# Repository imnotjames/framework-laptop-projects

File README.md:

# Framework Laptop projects

## eDP port

The framework laptop uses the [I-PEX Cabline-UM 20879-040E-01](https://www.i-pex.com/product/cabline-um)
for interacting with the eDP port - and I want to use it for things other than the framework laptop display kit.

* [Framework eDP 20879-040E-01 Breakout](./breakout/)

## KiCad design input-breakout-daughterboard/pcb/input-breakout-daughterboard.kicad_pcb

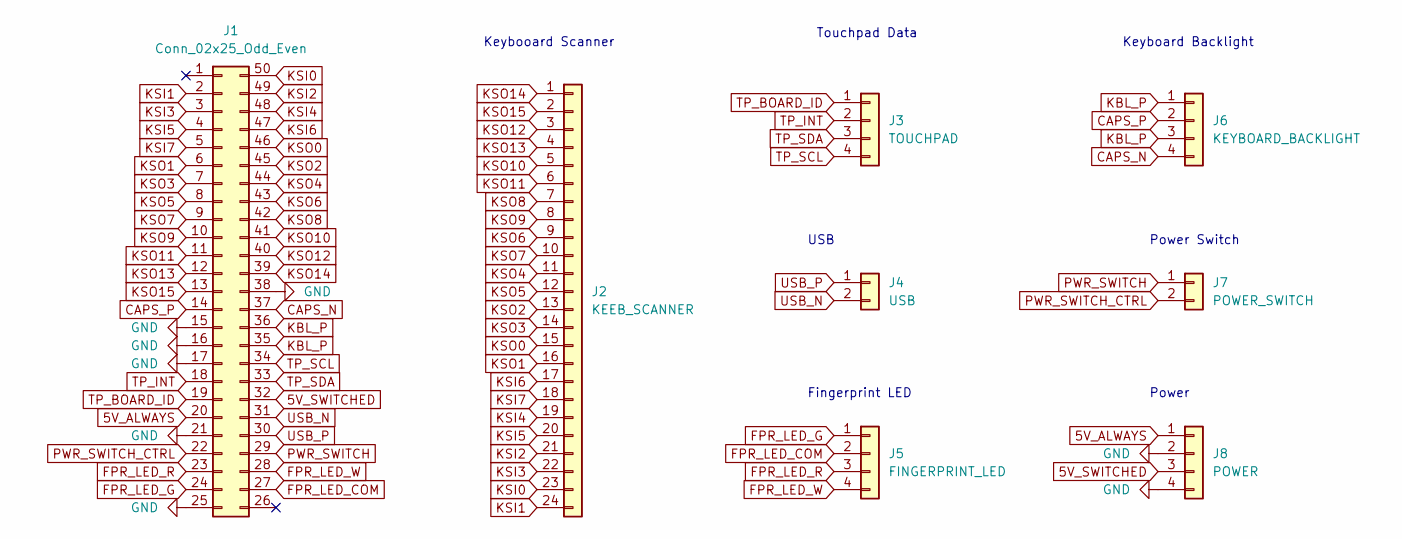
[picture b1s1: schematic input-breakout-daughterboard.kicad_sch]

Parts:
J1: Conn_02x25_Odd_Even; 10156001-051100LF
J2: KEEB_SCANNER; PinSocket_2x12_P2.54mm_Vertical
J3: TOUCHPAD; PinSocket_2x02_P2.54mm_Vertical
J4: USB; PinSocket_1x02_P2.54mm_Vertical
J5: FINGERPRINT_LED; PinSocket_2x02_P2.54mm_Vertical
J6: KEYBOARD_BACKLIGHT; PinSocket_2x02_P2.54mm_Vertical
J7: POWER_SWITCH; PinSocket_1x02_P2.54mm_Vertical
J8: POWER; PinSocket_2x02_P2.54mm_Vertical

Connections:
5V_ALWAYS: J1.20, J8.1
5V_SWITCHED: J1.32, J8.3
CAPS_N: J1.37, J6.4
CAPS_P: J1.14, J6.2
FPR_LED_COM: J1.27, J5.2
FPR_LED_G: J1.24, J5.1
FPR_LED_R: J1.23, J5.3
FPR_LED_W: J1.28, J5.4
GND: J1.15, J1.16, J1.17, J1.21, J1.25, J1.38, J8.2, J8.4
KBL_P: J1.35, J1.36, J6.1, J6.3
KSI0: J1.50, J2.23
KSI1: J1.2, J2.24
KSI2: J1.49, J2.21
KSI3: J1.3, J2.22
KSI4: J1.48, J2.19
KSI5: J1.4, J2.20
KSI6: J1.47, J2.17
KSI7: J1.5, J2.18
KSO0: J1.46, J2.15
KSO1: J1.6, J2.16
KSO2: J1.45, J2.13
KSO3: J1.7, J2.14
KSO4: J1.44, J2.11
KSO5: J1.8, J2.12
KSO6: J1.43, J2.9
KSO7: J1.9, J2.10
KSO8: J1.42, J2.7
KSO9: J1.10, J2.8
KSO10: J1.41, J2.5
KSO11: J1.11, J2.6
KSO12: J1.40, J2.3
KSO13: J1.12, J2.4
KSO14: J1.39, J2.1
KSO15: J1.13, J2.2
PWR_SWITCH: J1.29, J7.1
PWR_SWITCH_CTRL: J1.22, J7.2
TP_BOARD_ID: J1.19, J3.1
TP_INT: J1.18, J3.2
TP_SCL: J1.34, J3.4
TP_SDA: J1.33, J3.3
USB_N: J1.31, J4.2
USB_P: J1.30, J4.1

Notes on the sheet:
Power
Touchpad Data
USB
Keybooard Scanner
Keyboard Backlight
Power Switch
Fingerprint LED

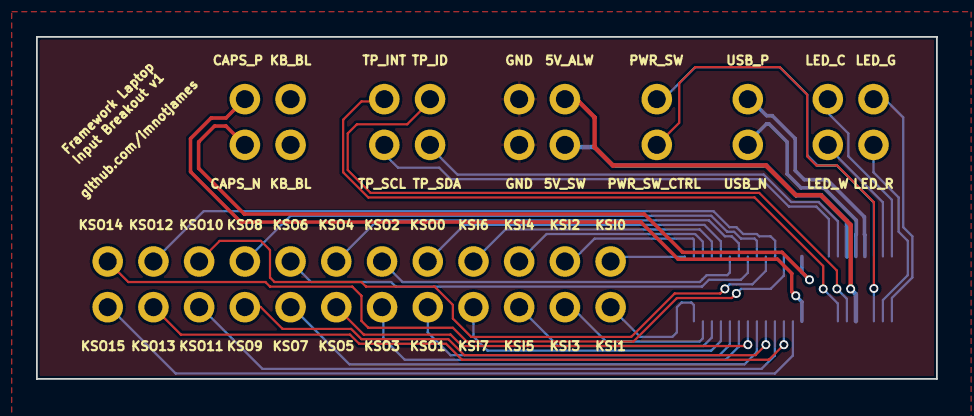
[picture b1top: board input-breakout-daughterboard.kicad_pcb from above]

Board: 2 copper layers, 50.0 x 19.0 mm, 8 parts (1 on the bottom side), 42 nets.

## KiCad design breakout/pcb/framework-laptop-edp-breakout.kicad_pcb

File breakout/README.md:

# Cabline-UM Breakout Board

This is a breakout board for the Framework Mainboard eDP connection via Cabline-UM 20879-040E-01.

This does not work with the standard Framework laptop cable that comes with the display kit.
The display kit seems to come with a cable that is on one half the cabline-um and on the other half is a cabline-vs
plug.

Instead, this breakout uses the Cabline-UM 20879-040E-01 to connect to the Framework mainboard, allowing you access
to all of the pins in a breakout.

Don't expect to be able to use it for reliable high-speed display-port connections but it may work for
basic prototypes or confirming the touchscreen.

## Fabrication

I've had decent luck getting this fabricated on JLCPCB - it was made with their limitations and tolerances in mind.

## Assembly Hints

If you can figure out how to assemble this by hand with a soldering iron please let me know how!  Most of the pins are hidden
behind a shield so the only way I was able to manage this was with a hot plate and solder paste.

## Bill of Materials

* [I-PEX 20879-040E-01](https://www.digikey.com/en/products/detail/i-pex/20879-040E-01/14312094)
* [A 40 Position Header Connector with 2.54mm pitch](https://www.digikey.com/en/products/detail/sullins-connector-solutions/PPTC202LFBN-RC/807240)
* [A Cabline-UM plug such as the 81466-100B-02-D](https://www.digikey.com/en/products/detail/i-pex/81466-100B-02-D/14312108)

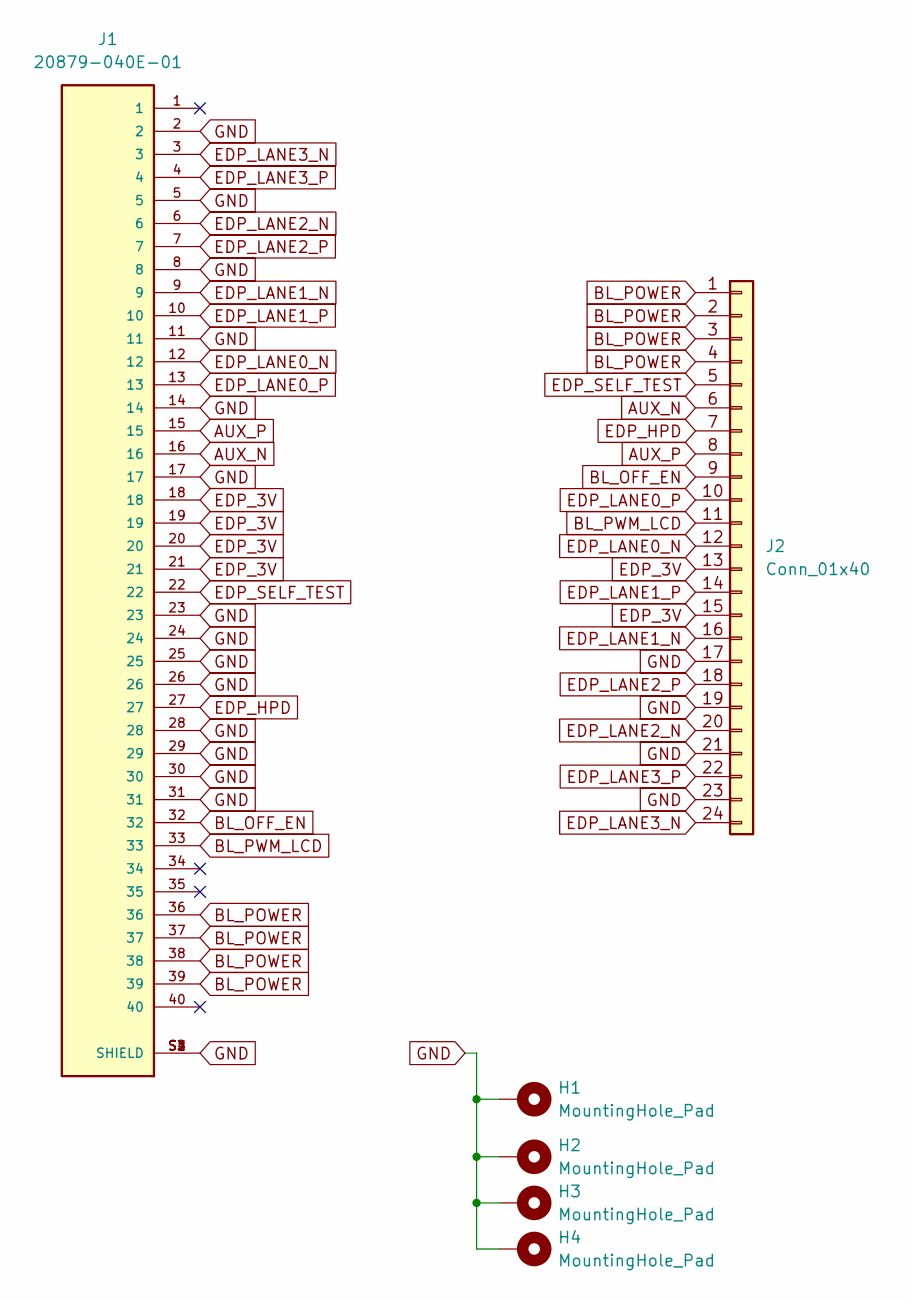
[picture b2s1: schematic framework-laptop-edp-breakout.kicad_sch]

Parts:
H1, H2, H3, H4: MountingHole_Pad; MountingHole_2.2mm_M2_DIN965_Pad
J1: 20879-040E-01; IPEX_20455-040E-76; PARTREV 11
J2: Conn_01x40; PinSocket_2x12_P2.54mm_Vertical

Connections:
AUX_N: J1.16, J2.6
AUX_P: J1.15, J2.8
BL_OFF_EN: J1.32, J2.9
BL_POWER: J1.36, J1.37, J1.38, J1.39, J2.1, J2.2, J2.3, J2.4
BL_PWM_LCD: J1.33, J2.11
EDP_3V: J1.18, J1.19, J1.20, J1.21, J2.13, J2.15
EDP_HPD: J1.27, J2.7
EDP_LANE0_N: J1.12, J2.12
EDP_LANE0_P: J1.13, J2.10
EDP_LANE1_N: J1.9, J2.16
EDP_LANE1_P: J1.10, J2.14
EDP_LANE2_N: J1.6, J2.20
EDP_LANE2_P: J1.7, J2.18
EDP_LANE3_N: J1.3, J2.24
EDP_LANE3_P: J1.4, J2.22
EDP_SELF_TEST: J1.22, J2.5
GND: H1.1, H2.1, H3.1, H4.1, J1.2, J1.5, J1.8, J1.11, J1.14, J1.17, J1.23, J1.24, J1.25, J1.26, J1.28, J1.29, J1.30, J1.31, J1.S1 (SHIELD), J1.S2 (SHIELD), J1.S3 (SHIELD), J1.S4 (SHIELD), J2.17, J2.19, J2.21, J2.23

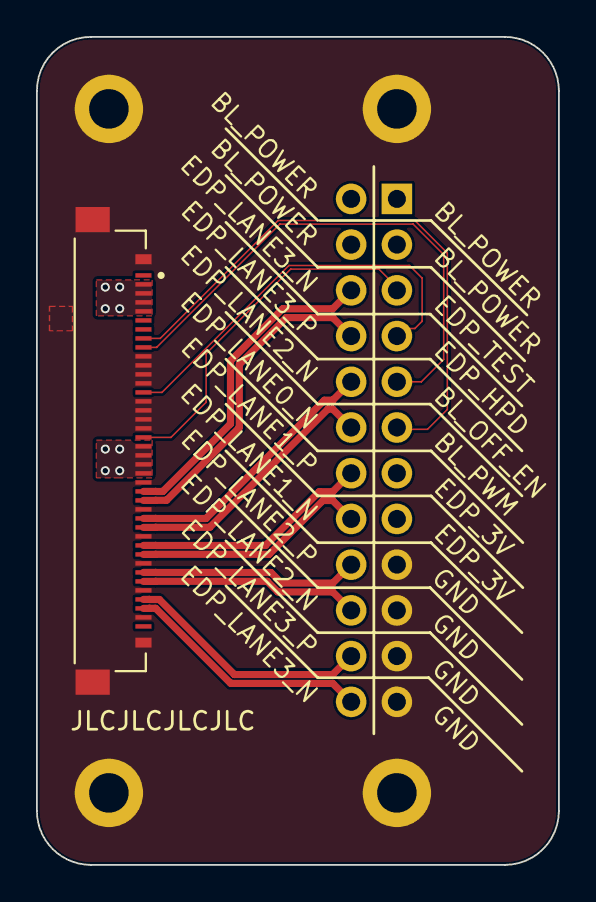
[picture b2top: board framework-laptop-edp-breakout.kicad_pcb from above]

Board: 2 copper layers, 29.0 x 46.0 mm, 6 parts (0 on the bottom side), 17 nets.

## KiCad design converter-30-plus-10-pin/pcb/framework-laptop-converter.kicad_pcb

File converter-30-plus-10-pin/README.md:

# Converter for Framework Laptop to 30+10pin 

This converts the framework laptop's 4 lane eDP to the 2 lane used in lower resolution screens.

In particular, this is aimed to allow us to easily interact with the [NV126B5M-N41][amazon] but it's not
exactly tested.

[amazon]: https://www.amazon.com/VSDISPLAY-NV126B5M-N41-12-6inch1920X515-Controller-VS-RTD2556HM-V1/dp/B08FJ33247

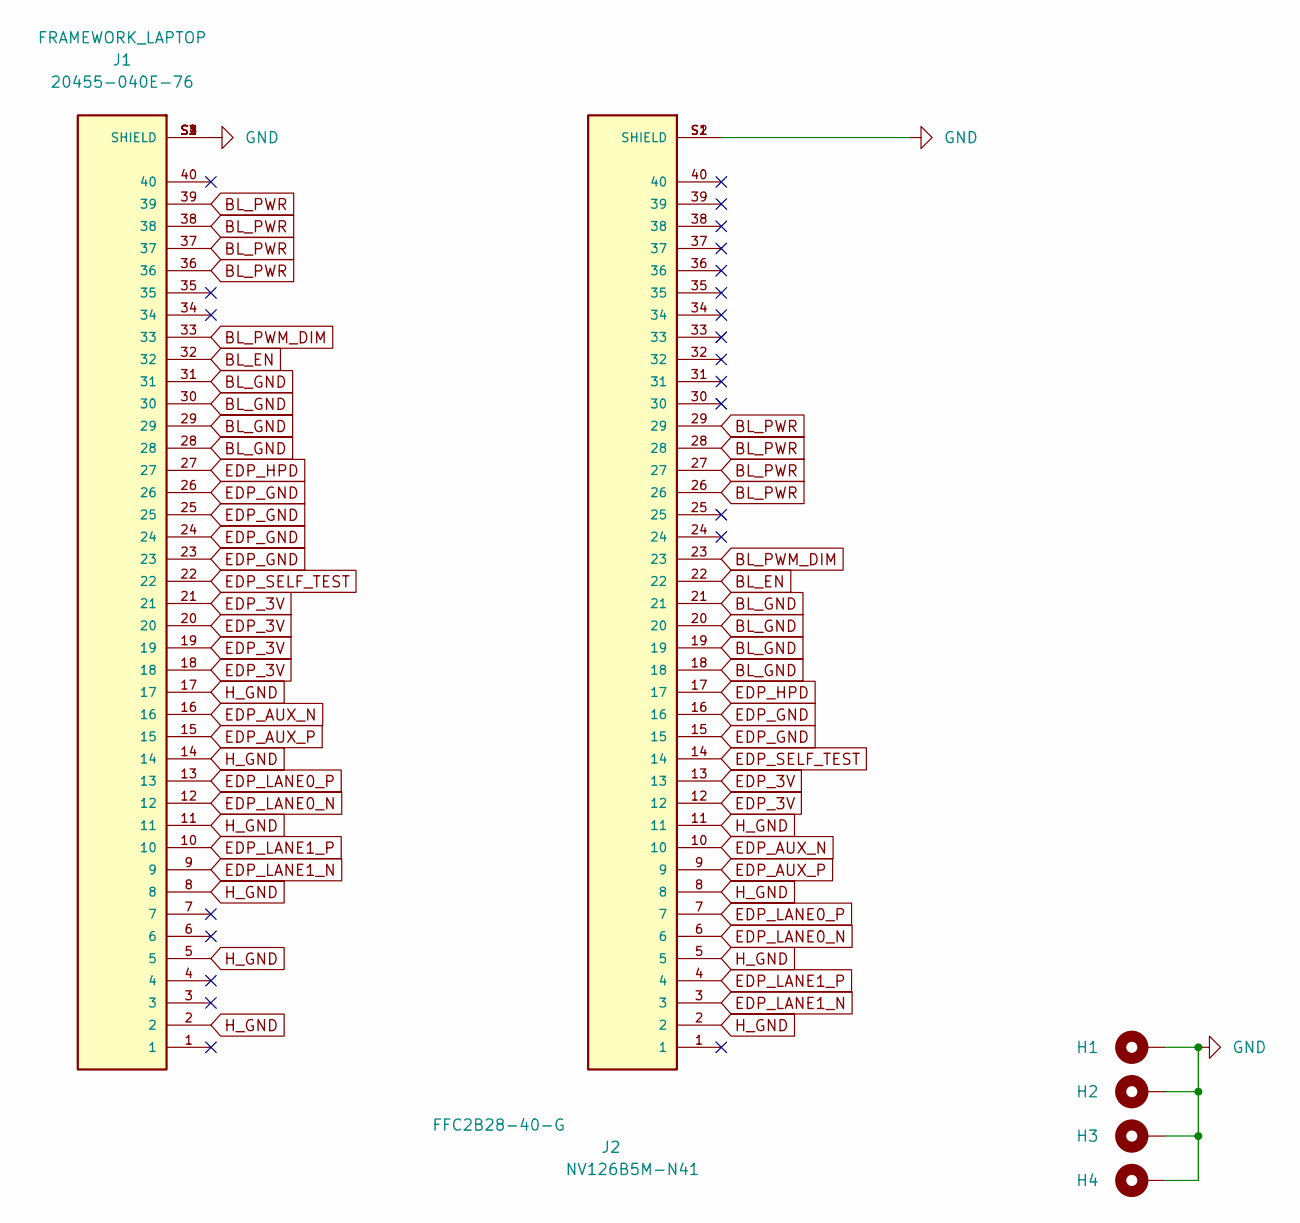
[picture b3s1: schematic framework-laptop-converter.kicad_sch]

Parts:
H1, H2, H3, H4: MountingHole_Pad; MountingHole_2.2mm_M2_Pad
J1: 20455-040E-76; IPEX_20455-040E-76; PARTREV 11
J2: FFC2B28-40-G; GCT_FFC2B28-40-G; PARTREV A

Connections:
BL_EN: J1.32, J2.22
BL_GND: J1.28, J1.29, J1.30, J1.31, J2.18, J2.19, J2.20, J2.21
BL_PWM_DIM: J1.33, J2.23
BL_PWR: J1.36, J1.37, J1.38, J1.39, J2.26, J2.27, J2.28, J2.29
EDP_3V: J1.18, J1.19, J1.20, J1.21, J2.12, J2.13
EDP_AUX_N: J1.16, J2.10
EDP_AUX_P: J1.15, J2.9
EDP_GND: J1.23, J1.24, J1.25, J1.26, J2.15, J2.16
EDP_HPD: J1.27, J2.17
EDP_LANE0_N: J1.12, J2.6
EDP_LANE0_P: J1.13, J2.7
EDP_LANE1_N: J1.9, J2.3
EDP_LANE1_P: J1.10, J2.4
EDP_SELF_TEST: J1.22, J2.14
GND: H1.1, H2.1, H3.1, H4.1, J1.S1 (SHIELD), J1.S2 (SHIELD), J1.S3 (SHIELD), J1.S4 (SHIELD), J2.S1 (SHIELD), J2.S2 (SHIELD)
H_GND: J1.2, J1.5, J1.8, J1.11, J1.14, J1.17, J2.2, J2.5, J2.8, J2.11

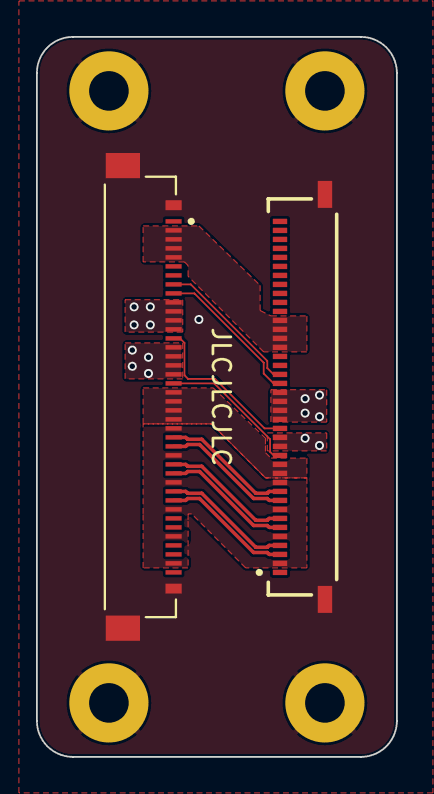
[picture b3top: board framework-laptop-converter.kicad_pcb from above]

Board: 2 copper layers, 20.0 x 40.0 mm, 6 parts (0 on the bottom side), 16 nets.

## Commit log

2022-07-30 better length matching
    I mean, impedance for a breakout seems kinda silly but it's worth it for learning, right?
2022-07-30 add a converter that maybe works maybe not
2022-07-30 add an amazon link
2022-08-01 fewer slots so this can be fabbed cheaper
2022-08-16 rework breakout because pins were wrong
    turns out pin out documentation from framework is reversed - pin 40 in pinouts.md is pin 1 on the data sheet for the ipex connector
2022-08-16 fix breakout labels on back
2022-08-16 finish up routing on breakout
2022-08-17 start migrating converter to framework's true pinout
2022-08-17 converter: route edp lane 0 and aux + fix shield to ground
2022-08-17 finish up edp converter with edp lane
2022-08-17 hide converter connector IDs
2022-08-18 mark converter as v4
2022-08-18 breakout v4
2022-08-19 bigger vias so jlcpcb gets off my case
2022-08-19 bigger vias on the breakout & remove some of em
2022-08-19 improve power rails on the breakout
2022-08-19 another via on bl_power in the breakout
2022-08-19 converter was crooked
2022-08-19 fix dimensions on converter
2022-09-07 redo converter to use the 20455-040E
2022-09-07 larger vias
2022-09-07 clean up footprints & connections
2022-09-16 for some reason these are backwards too
2022-09-16 make breakout use the bundled cable
2022-09-16 migrate breakout to new connector I guess
2022-09-16 bump converter rev number
2022-09-25 when you rush you make mistakes
2022-10-01 clean up converter to 2 layers & attach the BL_EN
2022-10-01 add revision to the breakout because I'm losing track
2022-10-02 start toying with a breakout board for the input connector
2022-10-03 input seems good enough for a v1
